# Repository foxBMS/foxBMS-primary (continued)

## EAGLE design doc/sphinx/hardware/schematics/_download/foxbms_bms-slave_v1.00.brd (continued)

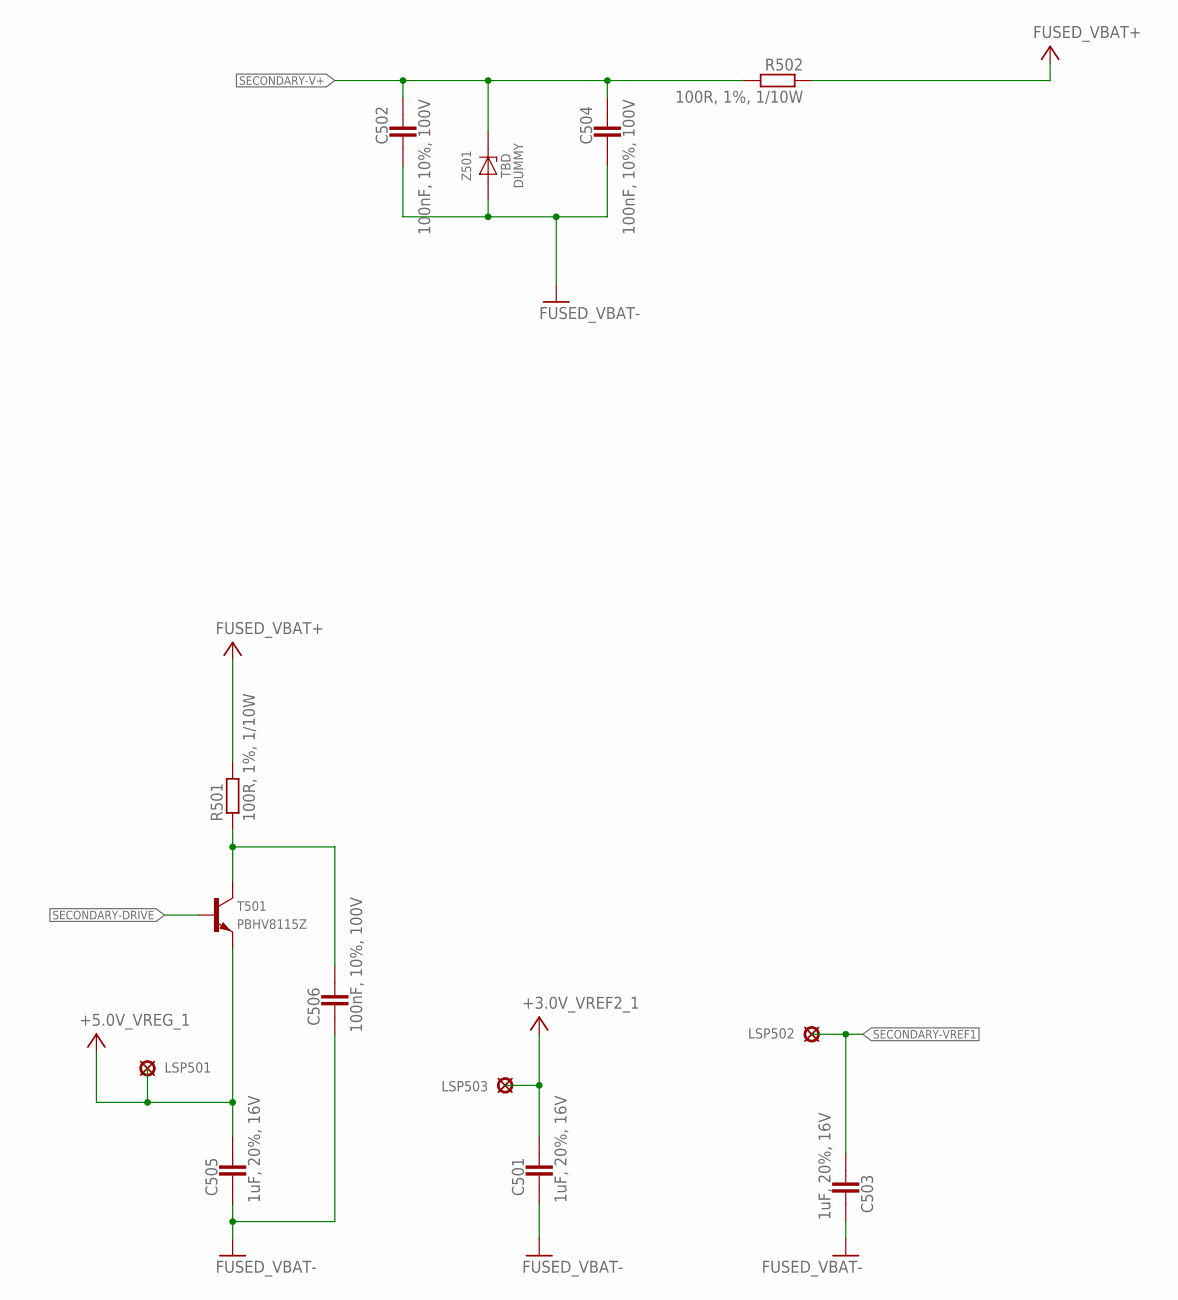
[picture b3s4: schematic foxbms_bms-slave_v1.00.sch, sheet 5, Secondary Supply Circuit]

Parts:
C501, C503, C505: 1uF, 20%, 16V; 0603
C502, C504, C506: 100nF, 10%, 100V; 0805
LSP501, LSP502, LSP503: PAD_2.0X1.5MM; PAD2.0X1.5MM
R501, R502: 100R, 1%, 1/10W; 0603
T501: PBHV8115Z; D_SMD_SOT223_(SC-73)_R_NXP_REV01
Z501: 60V,500mW; D_SMD_SOD-123_R_ON_REV01

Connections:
+3.0V_VREF2_1: C501.2, LSP503.P$1; also elsewhere on the board
+5.0V_VREG_1: C505.2, LSP501.P$1, T501.3 (E); also elsewhere on the board
FUSED_VBAT+: R501.2, R502.1; also elsewhere on the board
FUSED_VBAT-: C501.1, C502.2, C503.1, C504.2, C505.1, C506.1, Z501.A; also elsewhere on the board
unnamed: C506.2, R501.1, T501.2 (C), T501.4 (C)
SECONDARY-DRIVE: T501.1 (B); also elsewhere on the board
SECONDARY-V+: C502.1, C504.1, R502.2, Z501.K (C); also elsewhere on the board
SECONDARY-VREF1: C503.2, LSP502.P$1; also elsewhere on the board

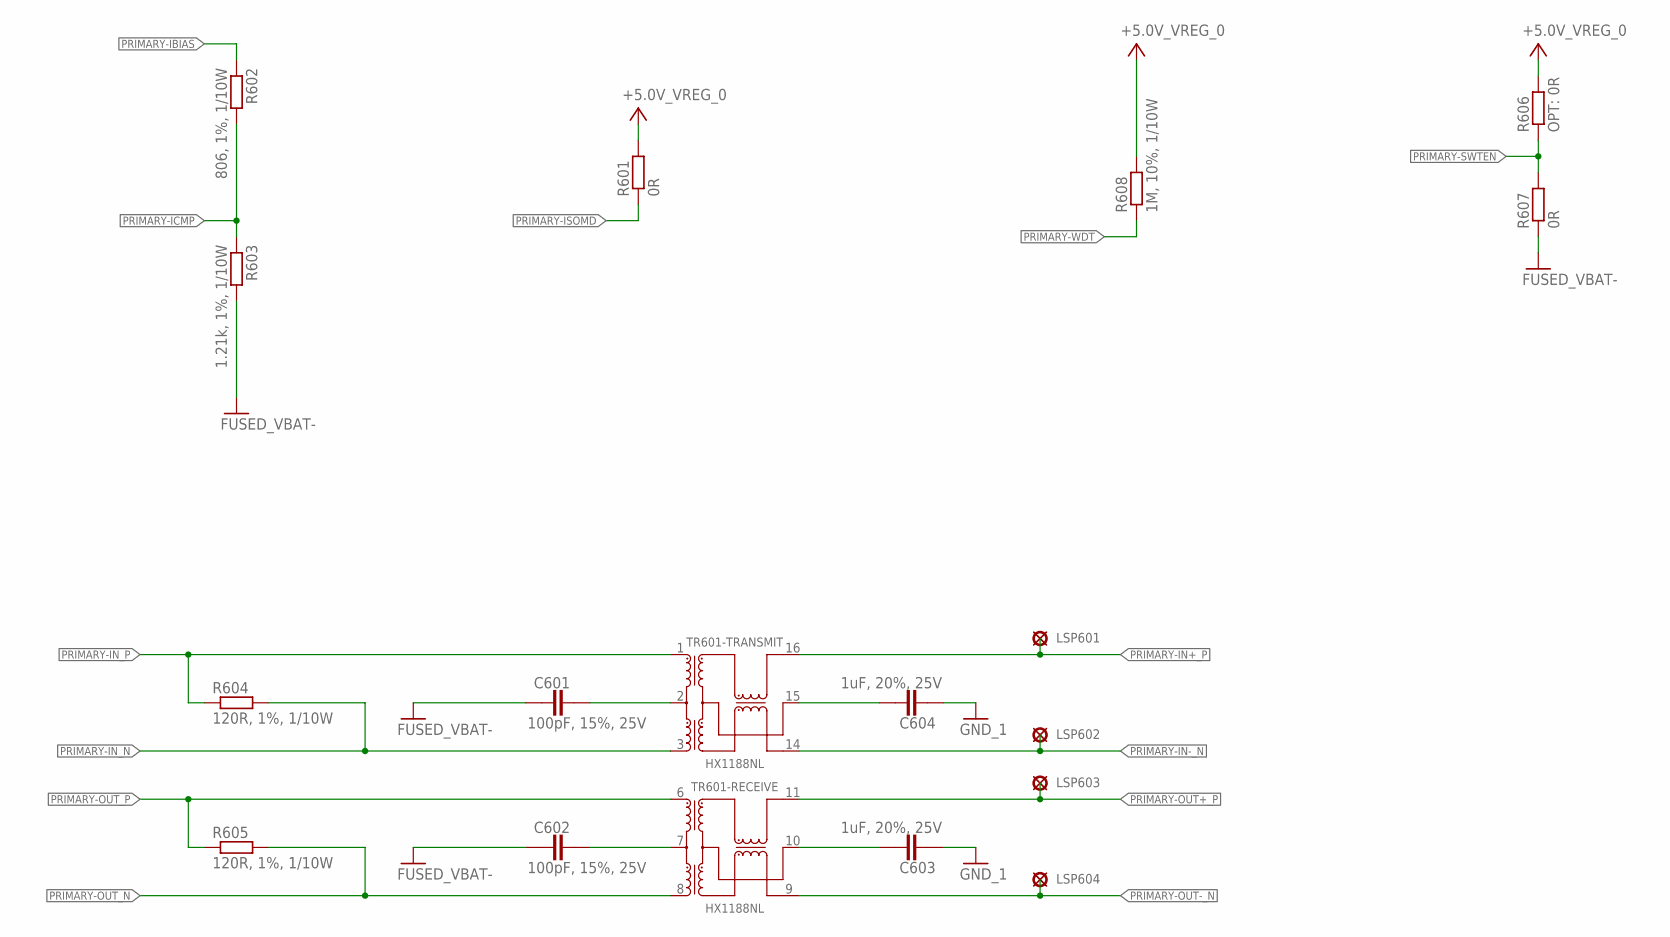
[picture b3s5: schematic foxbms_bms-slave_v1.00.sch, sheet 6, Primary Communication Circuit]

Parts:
C601, C602: 100pF, 15%, 25V; 0603
C603, C604: 1uF, 20%, 25V; 0603
LSP601, LSP602, LSP603, LSP604: PAD_2.0X1.5MM; PAD2.0X1.5MM
R601, R607: 0R; 0603
R602: 806, 1%, 1/10W; 0603
R603: 1.21k, 1%, 1/10W; 0603
R604, R605: 120R, 1%, 1/10W; 0603
R606: OPT: 0R; 0603
R608: 1M, 10%, 1/10W; 0603
TR601: HX1188NL; TR_SMD_SOIC-16_(12,70MMX9,53MMX5,97MM)_R_PULSE_REV01

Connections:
+5.0V_VREG_0: R601.2, R606.2, R608.2; also elsewhere on the board
FUSED_VBAT-: C601.1, C602.1, R603.2, R607.1; also elsewhere on the board
GND_1: C603.1, C604.1; also elsewhere on the board
unnamed: C601.2, TR601.2 (CT)
unnamed: C602.2, TR601.7 (CT)
unnamed: C604.2, TR601.15 (CMT)
unnamed: C603.2, TR601.10 (CMT)
PRIMARY-IBIAS: R602.1; also elsewhere on the board
PRIMARY-ICMP: R602.2, R603.1; also elsewhere on the board
PRIMARY-IN+_P: LSP601.P$1, TR601.16 (X+); also elsewhere on the board
PRIMARY-IN-_N: LSP602.P$1, TR601.14 (X-); also elsewhere on the board
PRIMARY-IN_N: R604.2, TR601.3 (D-); also elsewhere on the board
PRIMARY-IN_P: R604.1, TR601.1 (D+); also elsewhere on the board
PRIMARY-ISOMD: R601.1; also elsewhere on the board
PRIMARY-OUT+_P: LSP603.P$1, TR601.11 (X+); also elsewhere on the board
PRIMARY-OUT-_N: LSP604.P$1, TR601.9 (X-); also elsewhere on the board
PRIMARY-OUT_N: R605.2, TR601.8 (D-); also elsewhere on the board
PRIMARY-OUT_P: R605.1, TR601.6 (D+); also elsewhere on the board
PRIMARY-SWTEN: R606.1, R607.2; also elsewhere on the board
PRIMARY-WDT: R608.1; also elsewhere on the board

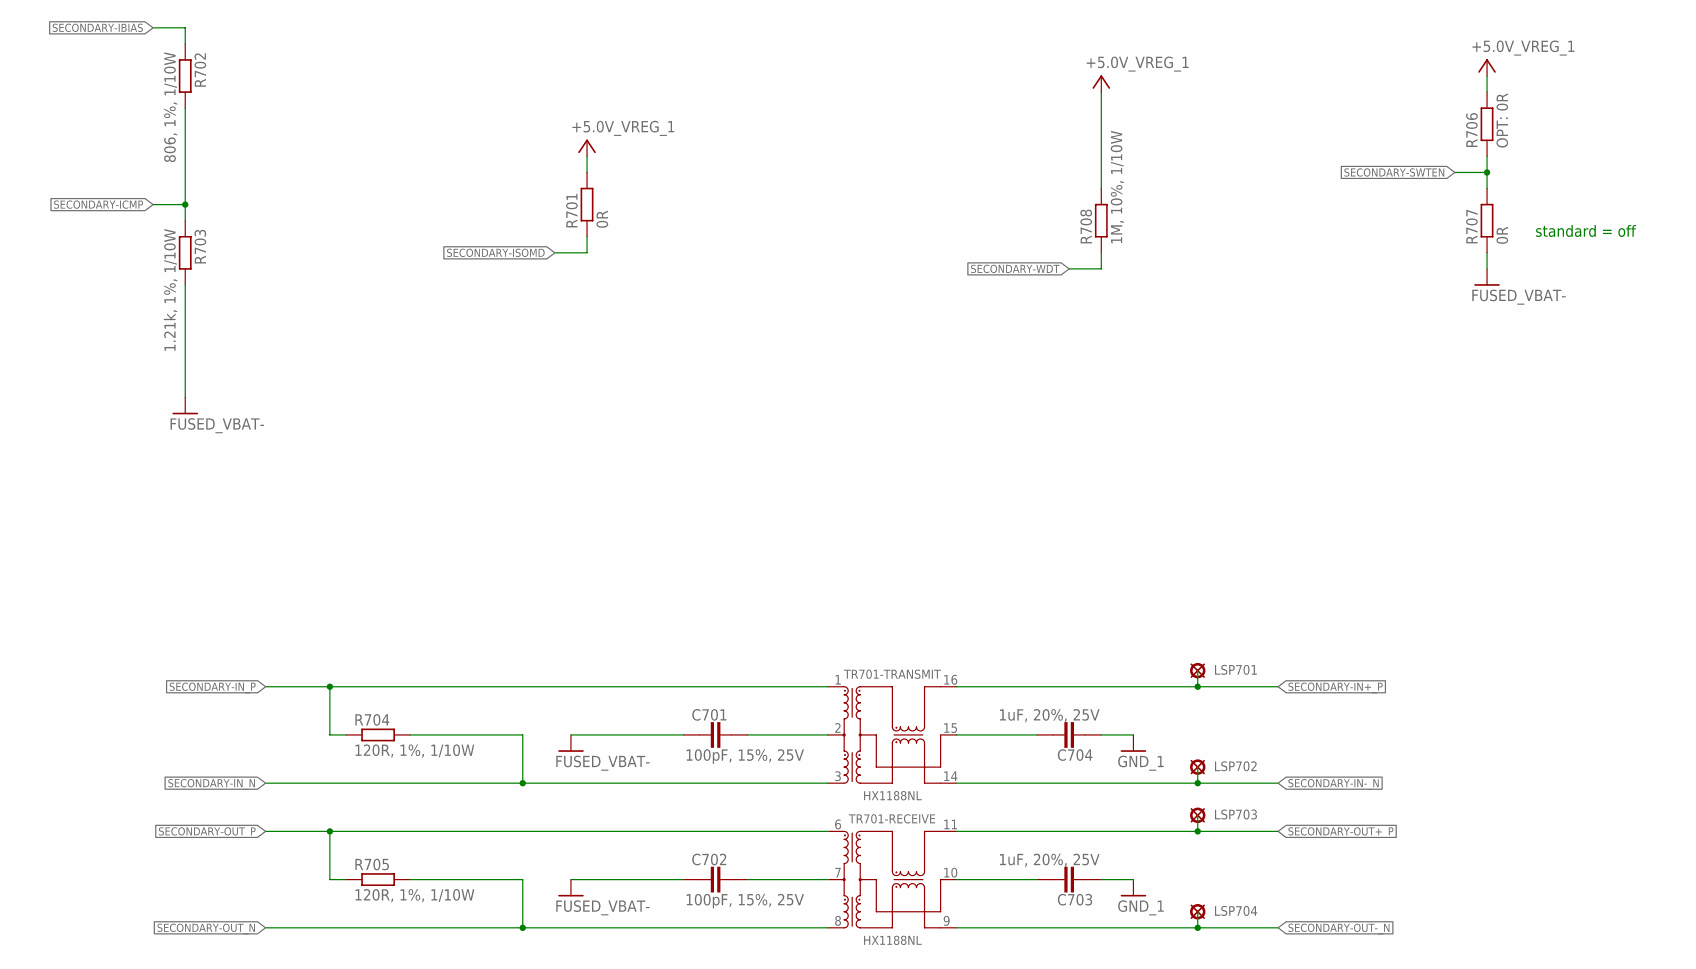
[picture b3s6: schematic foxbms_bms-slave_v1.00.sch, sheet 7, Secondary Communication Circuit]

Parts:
C701, C702: 100pF, 15%, 25V; 0603
C703, C704: 1uF, 20%, 25V; 0603
LSP701, LSP702, LSP703, LSP704: PAD_2.0X1.5MM; PAD2.0X1.5MM
R701, R707: 0R; 0603
R702: 806, 1%, 1/10W; 0603
R703: 1.21k, 1%, 1/10W; 0603
R704, R705: 120R, 1%, 1/10W; 0603
R706: OPT: 0R; 0603
R708: 1M, 10%, 1/10W; 0603
TR701: HX1188NL; TR_SMD_SOIC-16_(12,70MMX9,53MMX5,97MM)_R_PULSE_REV01

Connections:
+5.0V_VREG_1: R701.2, R706.2, R708.2; also elsewhere on the board
FUSED_VBAT-: C701.1, C702.1, R703.2, R707.1; also elsewhere on the board
GND_1: C703.1, C704.1; also elsewhere on the board
unnamed: C701.2, TR701.2 (CT)
unnamed: C702.2, TR701.7 (CT)
unnamed: C704.2, TR701.15 (CMT)
unnamed: C703.2, TR701.10 (CMT)
SECONDARY-IBIAS: R702.1; also elsewhere on the board
SECONDARY-ICMP: R702.2, R703.1; also elsewhere on the board
SECONDARY-IN+_P: LSP701.P$1, TR701.16 (X+); also elsewhere on the board
SECONDARY-IN-_N: LSP702.P$1, TR701.14 (X-); also elsewhere on the board
SECONDARY-IN_N: R704.2, TR701.3 (D-); also elsewhere on the board
SECONDARY-IN_P: R704.1, TR701.1 (D+); also elsewhere on the board
SECONDARY-ISOMD: R701.1; also elsewhere on the board
SECONDARY-OUT+_P: LSP703.P$1, TR701.11 (X+); also elsewhere on the board
SECONDARY-OUT-_N: LSP704.P$1, TR701.9 (X-); also elsewhere on the board
SECONDARY-OUT_N: R705.2, TR701.8 (D-); also elsewhere on the board
SECONDARY-OUT_P: R705.1, TR701.6 (D+); also elsewhere on the board
SECONDARY-SWTEN: R706.1, R707.2; also elsewhere on the board
SECONDARY-WDT: R708.1; also elsewhere on the board

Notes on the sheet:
standard = off

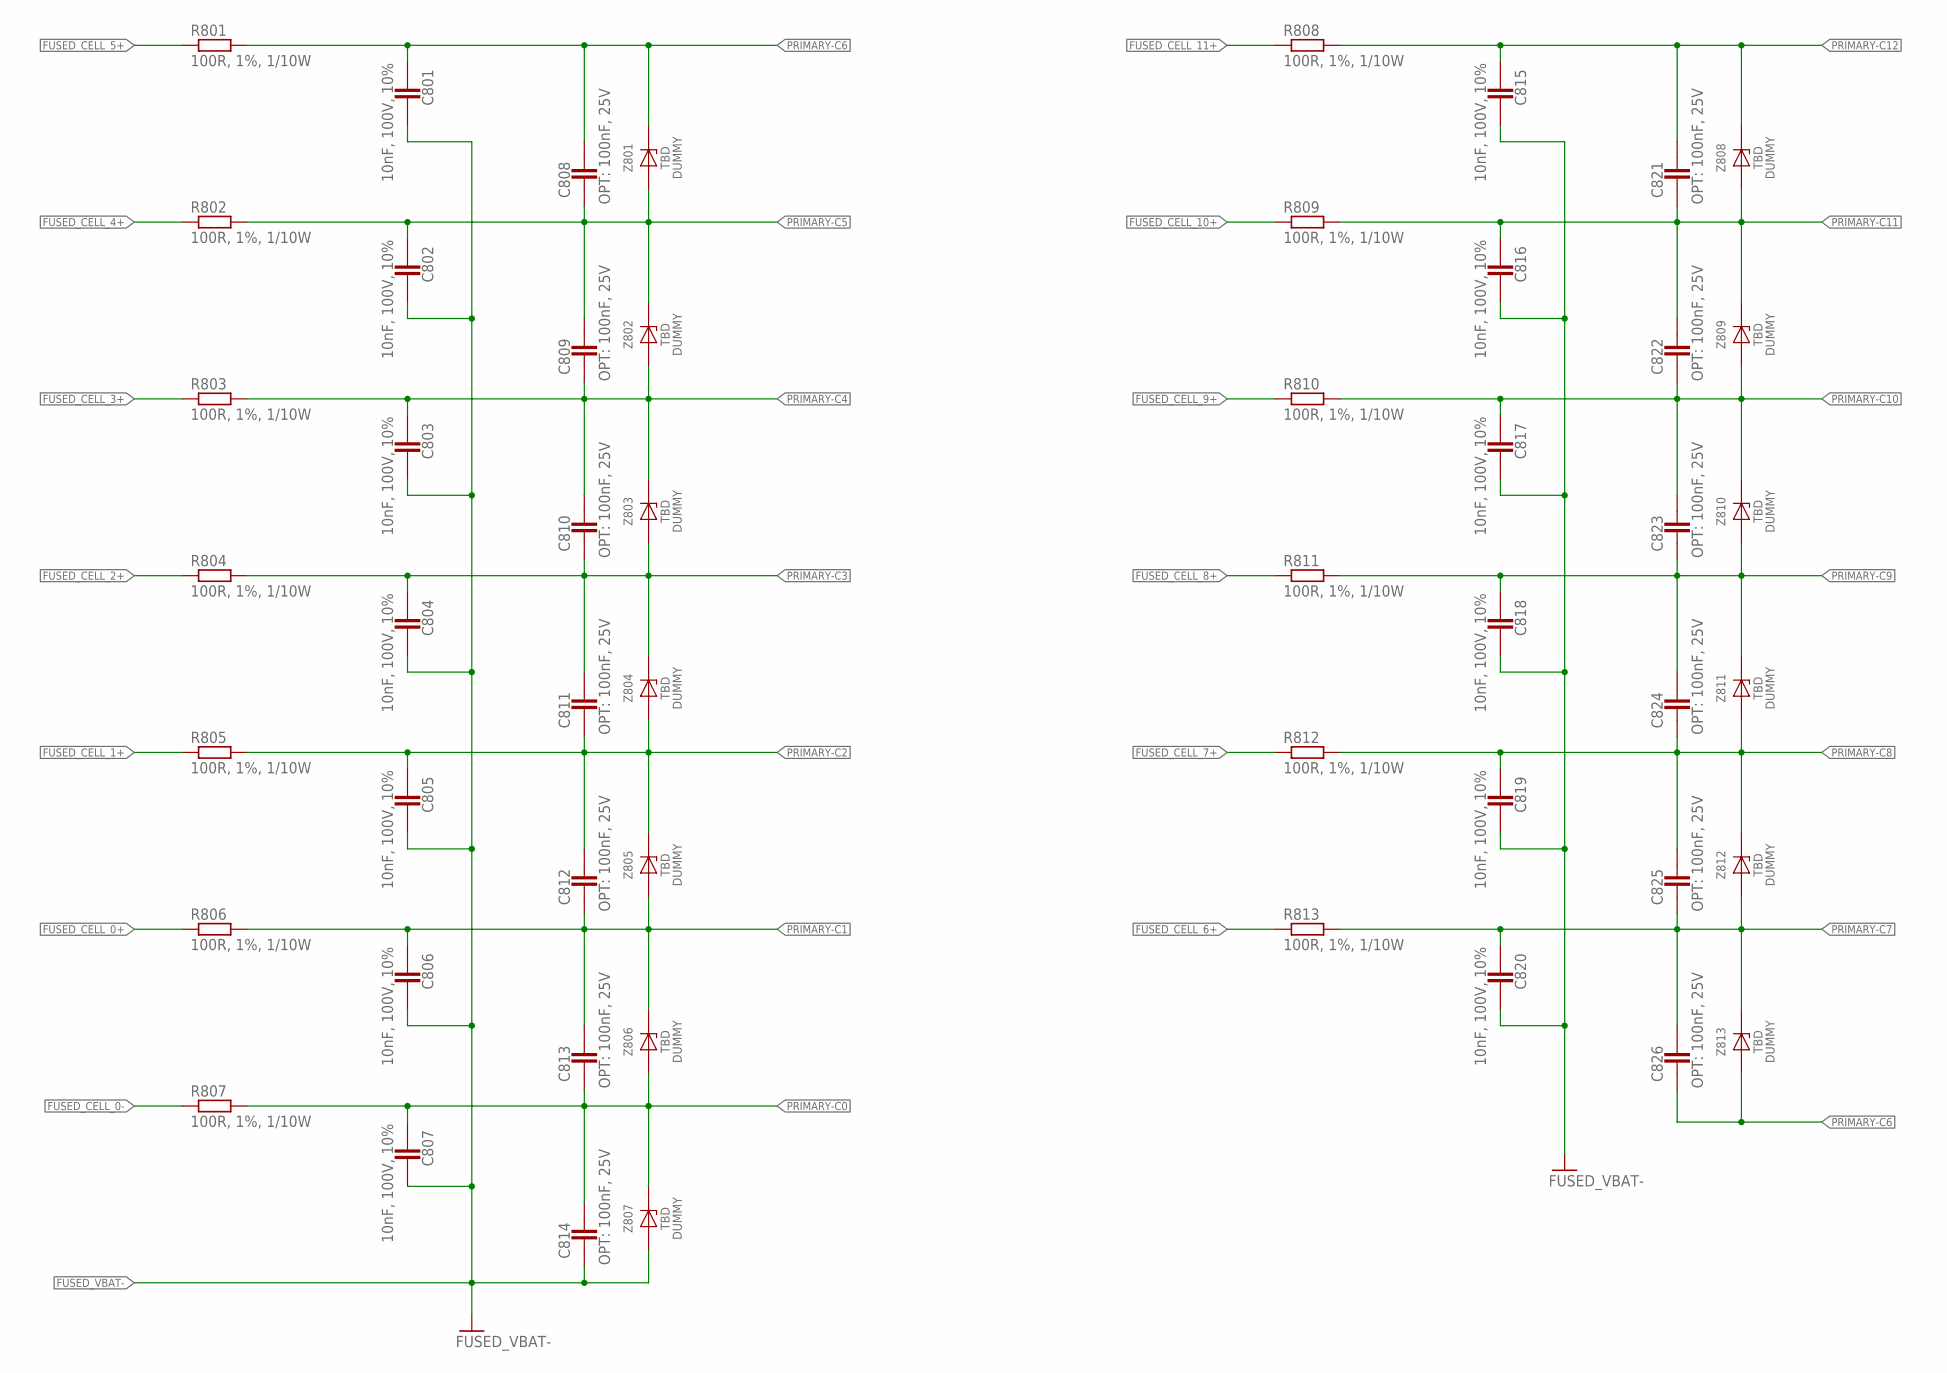
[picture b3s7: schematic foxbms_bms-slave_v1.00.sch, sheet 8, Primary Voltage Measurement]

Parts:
C801, C802, C803, C804, C805, C806, C807, C815, C816, C817, C818, C819, C820: 10nF, 100V, 10%; 0603
C808, C809, C810, C811, C812, C813, C814, C821, C822, C823, C824, C825, C826: OPT: 100nF, 25V; 0805
R801, R802, R803, R804, R805, R806, R807, R808, R809, R810, R811, R812, R813: 100R, 1%, 1/10W; 0603
Z801, Z802, Z803, Z804, Z805, Z806, Z807, Z808, Z809, Z810, Z811, Z812, Z813: 6.8V, 500mW; D_SMD_SOD-123_R_ON_REV01

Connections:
FUSED_CELL_0+: R806.1; also elsewhere on the board
FUSED_CELL_0-: R807.1; also elsewhere on the board
FUSED_CELL_1+: R805.1; also elsewhere on the board
FUSED_CELL_2+: R804.1; also elsewhere on the board
FUSED_CELL_3+: R803.1; also elsewhere on the board
FUSED_CELL_4+: R802.1; also elsewhere on the board
FUSED_CELL_5+: R801.1; also elsewhere on the board
FUSED_CELL_6+: R813.1; also elsewhere on the board
FUSED_CELL_7+: R812.1; also elsewhere on the board
FUSED_CELL_8+: R811.1; also elsewhere on the board
FUSED_CELL_9+: R810.1; also elsewhere on the board
FUSED_CELL_10+: R809.1; also elsewhere on the board
FUSED_CELL_11+: R808.1; also elsewhere on the board
FUSED_VBAT-: C801.2, C802.2, C803.2, C804.2, C805.2, C806.2, C807.2, C814.1, C815.2, C816.2, C817.2, C818.2, C819.2, C820.2, Z807.A; also elsewhere on the board
PRIMARY-C0: C807.1, C813.1, C814.2, R807.2, Z806.A, Z807.K (C); also elsewhere on the board
PRIMARY-C1: C806.1, C812.1, C813.2, R806.2, Z805.A, Z806.K (C); also elsewhere on the board
PRIMARY-C2: C805.1, C811.1, C812.2, R805.2, Z804.A, Z805.K (C); also elsewhere on the board
PRIMARY-C3: C804.1, C810.1, C811.2, R804.2, Z803.A, Z804.K (C); also elsewhere on the board
PRIMARY-C4: C803.1, C809.1, C810.2, R803.2, Z802.A, Z803.K (C); also elsewhere on the board
PRIMARY-C5: C802.1, C808.1, C809.2, R802.2, Z801.A, Z802.K (C); also elsewhere on the board
PRIMARY-C6: C801.1, C808.2, C826.1, R801.2, Z801.K (C), Z813.A; also elsewhere on the board
PRIMARY-C7: C820.1, C825.1, C826.2, R813.2, Z812.A, Z813.K (C); also elsewhere on the board
PRIMARY-C8: C819.1, C824.1, C825.2, R812.2, Z811.A, Z812.K (C); also elsewhere on the board
PRIMARY-C9: C818.1, C823.1, C824.2, R811.2, Z810.A, Z811.K (C); also elsewhere on the board
PRIMARY-C10: C817.1, C822.1, C823.2, R810.2, Z809.A, Z810.K (C); also elsewhere on the board
PRIMARY-C11: C816.1, C821.1, C822.2, R809.2, Z808.A, Z809.K (C); also elsewhere on the board
PRIMARY-C12: C815.1, C821.2, R808.2, Z808.K (C); also elsewhere on the board

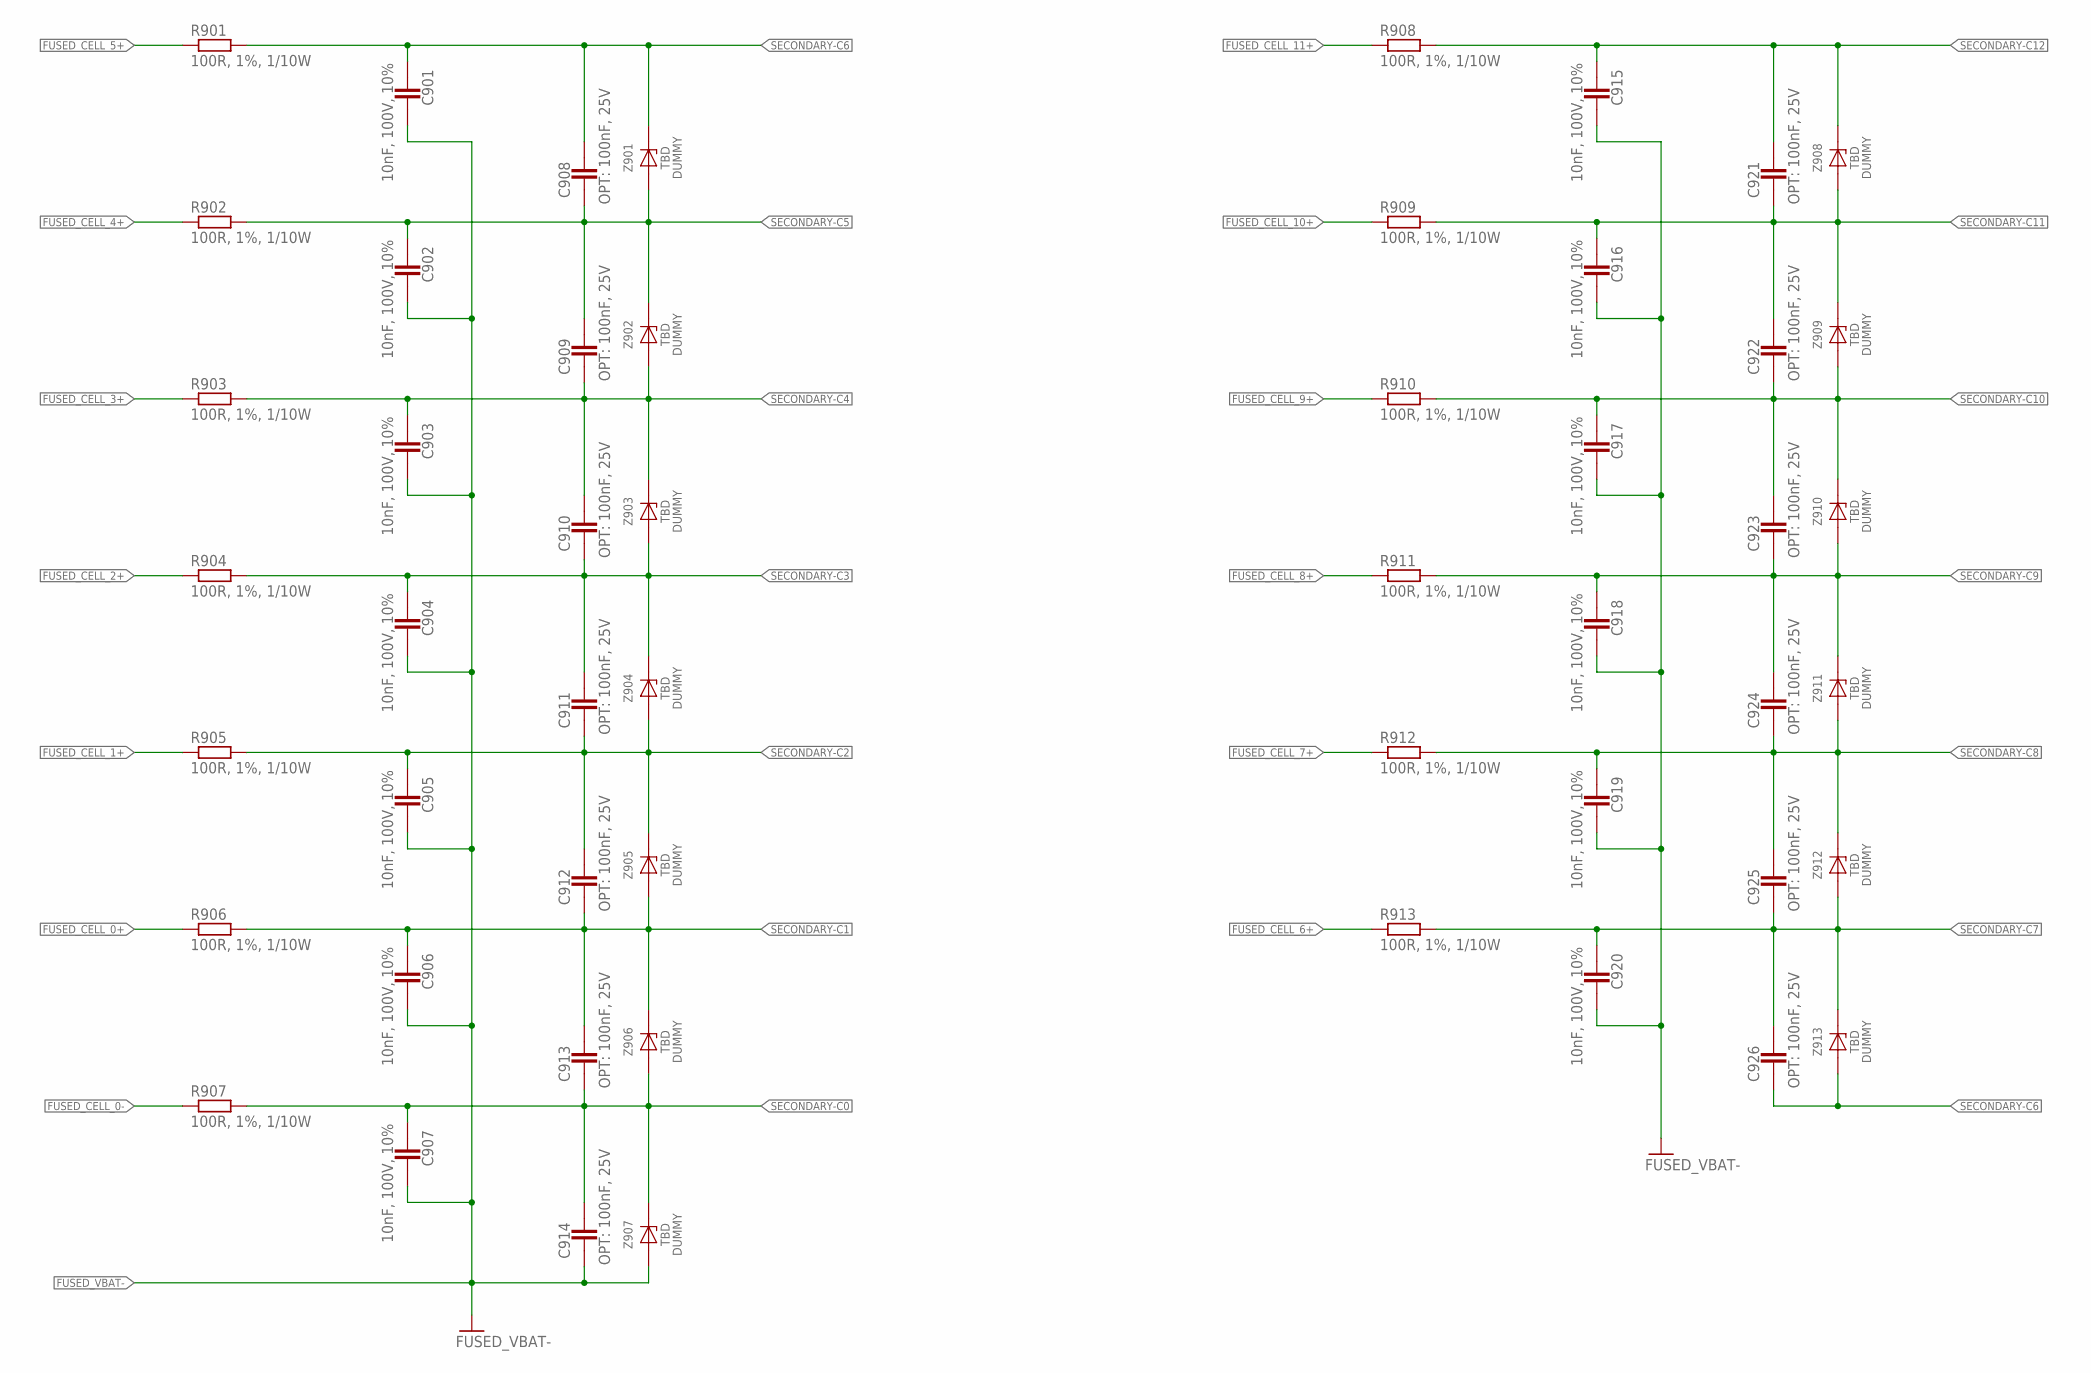
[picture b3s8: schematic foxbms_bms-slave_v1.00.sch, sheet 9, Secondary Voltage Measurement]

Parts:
C901, C902, C903, C904, C905, C906, C907, C915, C916, C917, C918, C919, C920: 10nF, 100V, 10%; 0603
C908, C909, C910, C911, C912, C913, C914, C921, C922, C923, C924, C925, C926: OPT: 100nF, 25V; 0805
R901, R902, R903, R904, R905, R906, R907, R908, R909, R910, R911, R912, R913: 100R, 1%, 1/10W; 0603
Z901, Z902, Z903, Z904, Z905, Z906, Z907, Z908, Z909, Z910, Z911, Z912, Z913: 6.8V, 500mW; D_SMD_SOD-123_R_ON_REV01

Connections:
FUSED_CELL_0+: R906.1; also elsewhere on the board
FUSED_CELL_0-: R907.1; also elsewhere on the board
FUSED_CELL_1+: R905.1; also elsewhere on the board
FUSED_CELL_2+: R904.1; also elsewhere on the board
FUSED_CELL_3+: R903.1; also elsewhere on the board
FUSED_CELL_4+: R902.1; also elsewhere on the board
FUSED_CELL_5+: R901.1; also elsewhere on the board
FUSED_CELL_6+: R913.1; also elsewhere on the board
FUSED_CELL_7+: R912.1; also elsewhere on the board
FUSED_CELL_8+: R911.1; also elsewhere on the board
FUSED_CELL_9+: R910.1; also elsewhere on the board
FUSED_CELL_10+: R909.1; also elsewhere on the board
FUSED_CELL_11+: R908.1; also elsewhere on the board
FUSED_VBAT-: C901.2, C902.2, C903.2, C904.2, C905.2, C906.2, C907.2, C914.1, C915.2, C916.2, C917.2, C918.2, C919.2, C920.2, Z907.A; also elsewhere on the board
SECONDARY-C0: C907.1, C913.1, C914.2, R907.2, Z906.A, Z907.K (C); also elsewhere on the board
SECONDARY-C1: C906.1, C912.1, C913.2, R906.2, Z905.A, Z906.K (C); also elsewhere on the board
SECONDARY-C2: C905.1, C911.1, C912.2, R905.2, Z904.A, Z905.K (C); also elsewhere on the board
SECONDARY-C3: C904.1, C910.1, C911.2, R904.2, Z903.A, Z904.K (C); also elsewhere on the board
SECONDARY-C4: C903.1, C909.1, C910.2, R903.2, Z902.A, Z903.K (C); also elsewhere on the board
SECONDARY-C5: C902.1, C908.1, C909.2, R902.2, Z901.A, Z902.K (C); also elsewhere on the board
SECONDARY-C6: C901.1, C908.2, C926.1, R901.2, Z901.K (C), Z913.A; also elsewhere on the board
SECONDARY-C7: C920.1, C925.1, C926.2, R913.2, Z912.A, Z913.K (C); also elsewhere on the board
SECONDARY-C8: C919.1, C924.1, C925.2, R912.2, Z911.A, Z912.K (C); also elsewhere on the board
SECONDARY-C9: C918.1, C923.1, C924.2, R911.2, Z910.A, Z911.K (C); also elsewhere on the board
SECONDARY-C10: C917.1, C922.1, C923.2, R910.2, Z909.A, Z910.K (C); also elsewhere on the board
SECONDARY-C11: C916.1, C921.1, C922.2, R909.2, Z908.A, Z909.K (C); also elsewhere on the board
SECONDARY-C12: C915.1, C921.2, R908.2, Z908.K (C); also elsewhere on the board

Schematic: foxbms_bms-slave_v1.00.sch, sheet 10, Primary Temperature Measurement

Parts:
C1001: 100nF, 20%, 16V; 0603
C1002, C1003, C1004: 1uF, 20%, 16V; 0603
C1005: 10nF, 20%, 16V; 0603
M1001, M1002: LTC1380CGN; IC_SMD_SSOP-16_(GN16)_R_LINEAR_REV01
O1001: LTC6255CS6; IC_SMD_TSOT-23-6_(S6)_R_LINEAR_REV01
R1001, R1002, R1003, R1004, R1005, R1006, R1007, R1008, R1009, R1010, R1011, R1012, R1013, R1014, R1015, R1016: 20k, 1%, 1/10W; 0603
R1017, R1018: 4.7k, 10%, 1/10W; 0603
R1019, R1021, R1023: N/A; 0603
R1020, R1022, R1024: 0R; 0603
R1025: 100R, 1%, 1/10W; 0603
SJ1001: OPT; SJ

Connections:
+3.0V_VREF2_0: C1001.2, R1001.2, R1002.2, R1003.2, R1004.2, R1005.2, R1006.2, R1007.2, R1008.2, R1009.2, R1010.2, R1011.2, R1012.2, R1013.2, R1014.2, R1015.2, R1016.2; also elsewhere on the board
+5.0V_VREG_0: C1002.2, C1003.2, C1004.2, M1001.16 (VCC), M1002.13 (A0), M1002.16 (VCC), O1001.6 (V+), R1017.2, R1018.2; also elsewhere on the board
FUSED_VBAT-: C1001.1, C1002.1, C1003.1, C1004.1, C1005.1, M1001.10 (VEE), M1001.11 (GND), M1001.12 (A1), M1001.13 (A0), M1002.10 (VEE), M1002.11 (GND), M1002.12 (A1), O1001.2 (V-); also elsewhere on the board
unnamed: O1001.1 (VOUT), O1001.4 (-), R1025.1
unnamed: O1001.5 (!SHDN), SJ1001.1
PRIMARY-GPIO0: R1023.2, R1024.2; also elsewhere on the board
PRIMARY-GPIO0-OPT: R1023.1; also elsewhere on the board
PRIMARY-GPIO2: SJ1001.2; also elsewhere on the board
PRIMARY-GPIO3: R1021.2, R1022.2; also elsewhere on the board
PRIMARY-GPIO3-OPT: R1021.1; also elsewhere on the board
PRIMARY-GPIO4: R1019.2, R1020.2; also elsewhere on the board
PRIMARY-GPIO4-OPT: R1019.1; also elsewhere on the board
PRIMARY-MUX-DATA: C1005.2, R1024.1, R1025.2
PRIMARY-OPA_IN: M1001.9 (DO), M1002.9 (DO), O1001.3 (+); also elsewhere on the board
PRIMARY-SCL: M1001.15 (SCL), M1002.15 (SCL), R1017.1, R1020.1; also elsewhere on the board
PRIMARY-SDA: M1001.14 (SDA), M1002.14 (SDA), R1018.1, R1022.1; also elsewhere on the board
T-SENSOR_0: M1001.1 (S0), R1015.1; also elsewhere on the board
T-SENSOR_1: M1001.2 (S1), R1013.1; also elsewhere on the board
T-SENSOR_2: M1001.3 (S2), R1011.1; also elsewhere on the board
T-SENSOR_3: M1001.4 (S3), R1009.1; also elsewhere on the board
T-SENSOR_4: M1001.5 (S4), R1007.1; also elsewhere on the board
T-SENSOR_5: M1001.6 (S5), R1005.1; also elsewhere on the board
T-SENSOR_6: M1001.7 (S6), R1003.1; also elsewhere on the board
T-SENSOR_7: M1001.8 (S7), R1001.1; also elsewhere on the board
T-SENSOR_8: M1002.1 (S0), R1016.1; also elsewhere on the board
T-SENSOR_9: M1002.2 (S1), R1014.1; also elsewhere on the board
T-SENSOR_10: M1002.3 (S2), R1012.1; also elsewhere on the board
T-SENSOR_11: M1002.4 (S3), R1010.1; also elsewhere on the board
T-SENSOR_12: M1002.5 (S4), R1008.1; also elsewhere on the board
T-SENSOR_13: M1002.6 (S5), R1006.1; also elsewhere on the board
T-SENSOR_14: M1002.7 (S6), R1004.1; also elsewhere on the board
T-SENSOR_15: M1002.8 (S7), R1002.1; also elsewhere on the board

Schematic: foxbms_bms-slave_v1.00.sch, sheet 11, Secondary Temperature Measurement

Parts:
C1101: 100nF, 20%, 16V; 0603
C1102, C1103, C1104: 1uF, 20%, 16V; 0603
C1105: 10nF, 20%, 16V; 0603
M1101, M1102: LTC1380CGN; IC_SMD_SSOP-16_(GN16)_R_LINEAR_REV01
O1101: LTC6255CS6; IC_SMD_TSOT-23-6_(S6)_R_LINEAR_REV01
R1101, R1102, R1103, R1104, R1105, R1106, R1107, R1108, R1109, R1110, R1111, R1112, R1113, R1114, R1115, R1116: 20k, 1%, 1/10W; 0603
R1117, R1118: 4.7k, 10%, 1/10W; 0603
R1119, R1121, R1123: OPT: 0R; 0603
R1120, R1122, R1124: 0R; 0603
R1125: 100R, 1%, 1/10W; 0603
SJ1101: OPT; SJ

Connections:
+3.0V_VREF2_1: C1101.2, R1101.2, R1102.2, R1103.2, R1104.2, R1105.2, R1106.2, R1107.2, R1108.2, R1109.2, R1110.2, R1111.2, R1112.2, R1113.2, R1114.2, R1115.2, R1116.2; also elsewhere on the board
+5.0V_VREG_1: C1102.2, C1103.2, C1104.2, M1101.16 (VCC), M1102.13 (A0), M1102.16 (VCC), O1101.6 (V+), R1117.2, R1118.2; also elsewhere on the board
FUSED_VBAT-: C1101.1, C1102.1, C1103.1, C1104.1, C1105.1, M1101.10 (VEE), M1101.11 (GND), M1101.12 (A1), M1101.13 (A0), M1102.10 (VEE), M1102.11 (GND), M1102.12 (A1), O1101.2 (V-); also elsewhere on the board
unnamed: O1101.5 (!SHDN), SJ1101.1
unnamed: O1101.1 (VOUT), O1101.4 (-), R1125.1
SECONDARY-GPIO0: R1123.2, R1124.2; also elsewhere on the board
SECONDARY-GPIO0-OPT: R1123.1; also elsewhere on the board
SECONDARY-GPIO2: SJ1101.2; also elsewhere on the board
SECONDARY-GPIO3: R1121.2, R1122.2; also elsewhere on the board
SECONDARY-GPIO3-OPT: R1121.1; also elsewhere on the board
SECONDARY-GPIO4: R1119.2, R1120.2; also elsewhere on the board
SECONDARY-GPIO4-OPT: R1119.1; also elsewhere on the board
SECONDARY-MUX-DATA: C1105.2, R1124.1, R1125.2
SECONDARY-OPA_IN: M1101.9 (DO), M1102.9 (DO), O1101.3 (+); also elsewhere on the board
SECONDARY-SCL: M1101.15 (SCL), M1102.15 (SCL), R1117.1, R1120.1; also elsewhere on the board
SECONDARY-SDA: M1101.14 (SDA), M1102.14 (SDA), R1118.1, R1122.1; also elsewhere on the board
T-SENSOR_16: M1101.1 (S0), R1115.1; also elsewhere on the board
T-SENSOR_17: M1101.2 (S1), R1113.1; also elsewhere on the board
T-SENSOR_18: M1101.3 (S2), R1111.1; also elsewhere on the board
T-SENSOR_19: M1101.4 (S3), R1109.1; also elsewhere on the board
T-SENSOR_20: M1101.5 (S4), R1107.1; also elsewhere on the board
T-SENSOR_21: M1101.6 (S5), R1105.1; also elsewhere on the board
T-SENSOR_22: M1101.7 (S6), R1103.1; also elsewhere on the board
T-SENSOR_23: M1101.8 (S7), R1101.1; also elsewhere on the board
T-SENSOR_24: M1102.1 (S0), R1116.1; also elsewhere on the board
T-SENSOR_25: M1102.2 (S1), R1114.1; also elsewhere on the board
T-SENSOR_26: M1102.3 (S2), R1112.1; also elsewhere on the board
T-SENSOR_27: M1102.4 (S3), R1110.1; also elsewhere on the board
T-SENSOR_28: M1102.5 (S4), R1108.1; also elsewhere on the board
T-SENSOR_29: M1102.6 (S5), R1106.1; also elsewhere on the board
T-SENSOR_30: M1102.7 (S6), R1104.1; also elsewhere on the board
T-SENSOR_31: M1102.8 (S7), R1102.1; also elsewhere on the board

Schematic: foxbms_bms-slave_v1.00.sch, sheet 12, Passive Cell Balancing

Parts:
R1201, R1202, R1203, R1204, R1205, R1206, R1207, R1208, R1209, R1210, R1211, R1212, R1219, R1220, R1221, R1222, R1223, R1224, R1225, R1226, R1227, R1228, R1229, R1230: 75R, 10%, 0.4W; 2010
R1213, R1214, R1215, R1216, R1217, R1218, R1231, R1232, R1233, R1234, R1235, R1236: 3.3k, 10%, 1/10W; 0603
T1201, T1202, T1203, T1204, T1205, T1206, T1207, T1208, T1209, T1210, T1211, T1212: NX2301P; D_SMD_SOT23_(TO-236AB)_R_NXP_REV01

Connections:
CELL0_FEEDBACK+: R1206.2, R1212.2, T1206.3 (D); also elsewhere on the board
CELL1_FEEDBACK+: R1205.2, R1211.2, T1205.3 (D); also elsewhere on the board
CELL2_FEEDBACK+: R1204.2, R1210.2, T1204.3 (D); also elsewhere on the board
CELL3_FEEDBACK+: R1203.2, R1209.2, T1203.3 (D); also elsewhere on the board
CELL4_FEEDBACK+: R1202.2, R1208.2, T1202.3 (D); also elsewhere on the board
CELL5_FEEDBACK+: R1201.2, R1207.2, T1201.3 (D); also elsewhere on the board
CELL6_FEEDBACK+: R1224.2, R1230.2, T1212.3 (D); also elsewhere on the board
CELL7_FEEDBACK+: R1223.2, R1229.2, T1211.3 (D); also elsewhere on the board
CELL8_FEEDBACK+: R1222.2, R1228.2, T1210.3 (D); also elsewhere on the board
CELL9_FEEDBACK+: R1221.2, R1227.2, T1209.3 (D); also elsewhere on the board
CELL10_FEEDBACK+: R1220.2, R1226.2, T1208.3 (D); also elsewhere on the board
CELL11_FEEDBACK+: R1219.2, R1225.2, T1207.3 (D); also elsewhere on the board
FUSED_CELL_0+: R1205.1, R1211.1, T1206.2 (S); also elsewhere on the board
FUSED_CELL_1+: R1204.1, R1210.1, T1205.2 (S); also elsewhere on the board
FUSED_CELL_2+: R1203.1, R1209.1, T1204.2 (S); also elsewhere on the board
FUSED_CELL_3+: R1202.1, R1208.1, T1203.2 (S); also elsewhere on the board
FUSED_CELL_4+: R1201.1, R1207.1, T1202.2 (S); also elsewhere on the board
FUSED_CELL_5+: R1224.1, R1230.1, T1201.2 (S); also elsewhere on the board
FUSED_CELL_6+: R1223.1, R1229.1, T1212.2 (S); also elsewhere on the board
FUSED_CELL_7+: R1222.1, R1228.1, T1211.2 (S); also elsewhere on the board
FUSED_CELL_8+: R1221.1, R1227.1, T1210.2 (S); also elsewhere on the board
FUSED_CELL_9+: R1220.1, R1226.1, T1209.2 (S); also elsewhere on the board
FUSED_CELL_10+: R1219.1, R1225.1, T1208.2 (S); also elsewhere on the board
FUSED_CELL_11+: T1207.2 (S); also elsewhere on the board
FUSED_VBAT-: R1206.1, R1212.1; also elsewhere on the board
unnamed: R1218.1, T1206.1 (G)
unnamed: R1216.1, T1205.1 (G)
unnamed: R1217.1, T1204.1 (G)
unnamed: R1215.1, T1203.1 (G)
unnamed: R1214.1, T1202.1 (G)
unnamed: R1213.1, T1201.1 (G)
unnamed: R1232.1, T1212.1 (G)
unnamed: R1236.1, T1211.1 (G)
unnamed: R1235.1, T1210.1 (G)
unnamed: R1234.1, T1209.1 (G)
unnamed: R1233.1, T1208.1 (G)
unnamed: R1231.1, T1207.1 (G)
S0: R1218.2; also elsewhere on the board
S1: R1216.2; also elsewhere on the board
S2: R1217.2; also elsewhere on the board
S3: R1215.2; also elsewhere on the board
S4: R1214.2; also elsewhere on the board
S5: R1213.2; also elsewhere on the board
S6: R1232.2; also elsewhere on the board
S7: R1236.2; also elsewhere on the board
S8: R1235.2; also elsewhere on the board
S9: R1234.2; also elsewhere on the board
S10: R1233.2; also elsewhere on the board
S11: R1231.2; also elsewhere on the board

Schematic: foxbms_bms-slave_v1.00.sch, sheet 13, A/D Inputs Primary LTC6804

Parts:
C1301, C1302: 1uF, 20%, 16V; 0603
M1301, M1302: LTC1380CGN; IC_SMD_SSOP-16_(GN16)_R_LINEAR_REV01
R1301, R1302, R1303, R1304, R1305, R1306, R1307, R1308, R1309, R1310, R1311, R1312, R1313, R1314, R1315, R1316: 10k, 10%, 1/10W; 0603

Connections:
+5.0V_VREG_0: C1301.2, C1302.2, M1301.12 (A1), M1301.16 (VCC), M1302.12 (A1), M1302.13 (A0), M1302.16 (VCC); also elsewhere on the board
FUSED_VBAT-: C1301.1, C1302.1, M1301.10 (VEE), M1301.11 (GND), M1301.13 (A0), M1302.10 (VEE), M1302.11 (GND), R1301.2, R1302.2, R1303.2, R1304.2, R1305.2, R1306.2, R1307.2, R1308.2, R1309.2, R1310.2, R1311.2, R1312.2, R1313.2, R1314.2, R1315.2, R1316.2; also elsewhere on the board
PRIMARY-OPA_IN: M1301.9 (DO), M1302.9 (DO); also elsewhere on the board
PRIMARY-SCL: M1301.15 (SCL), M1302.15 (SCL); also elsewhere on the board
PRIMARY-SDA: M1301.14 (SDA), M1302.14 (SDA); also elsewhere on the board
PRIMARY_D/A_INPUT_0: M1301.1 (S0), R1301.1; also elsewhere on the board
PRIMARY_D/A_INPUT_1: M1301.2 (S1), R1302.1; also elsewhere on the board
PRIMARY_D/A_INPUT_2: M1301.3 (S2), R1303.1; also elsewhere on the board
PRIMARY_D/A_INPUT_3: M1301.4 (S3), R1304.1; also elsewhere on the board
PRIMARY_D/A_INPUT_4: M1301.5 (S4), R1305.1; also elsewhere on the board
PRIMARY_D/A_INPUT_5: M1301.6 (S5), R1306.1; also elsewhere on the board
PRIMARY_D/A_INPUT_6: M1301.7 (S6), R1307.1; also elsewhere on the board
PRIMARY_D/A_INPUT_7: M1301.8 (S7), R1308.1; also elsewhere on the board
PRIMARY_D/A_INPUT_8: M1302.1 (S0), R1309.1; also elsewhere on the board
PRIMARY_D/A_INPUT_9: M1302.2 (S1), R1310.1; also elsewhere on the board
PRIMARY_D/A_INPUT_10: M1302.3 (S2), R1311.1; also elsewhere on the board
PRIMARY_D/A_INPUT_11: M1302.4 (S3), R1312.1; also elsewhere on the board
PRIMARY_D/A_INPUT_12: M1302.5 (S4), R1313.1; also elsewhere on the board
PRIMARY_D/A_INPUT_13: M1302.6 (S5), R1314.1; also elsewhere on the board
PRIMARY_D/A_INPUT_14: M1302.7 (S6), R1315.1; also elsewhere on the board
PRIMARY_D/A_INPUT_15: M1302.8 (S7), R1316.1; also elsewhere on the board
